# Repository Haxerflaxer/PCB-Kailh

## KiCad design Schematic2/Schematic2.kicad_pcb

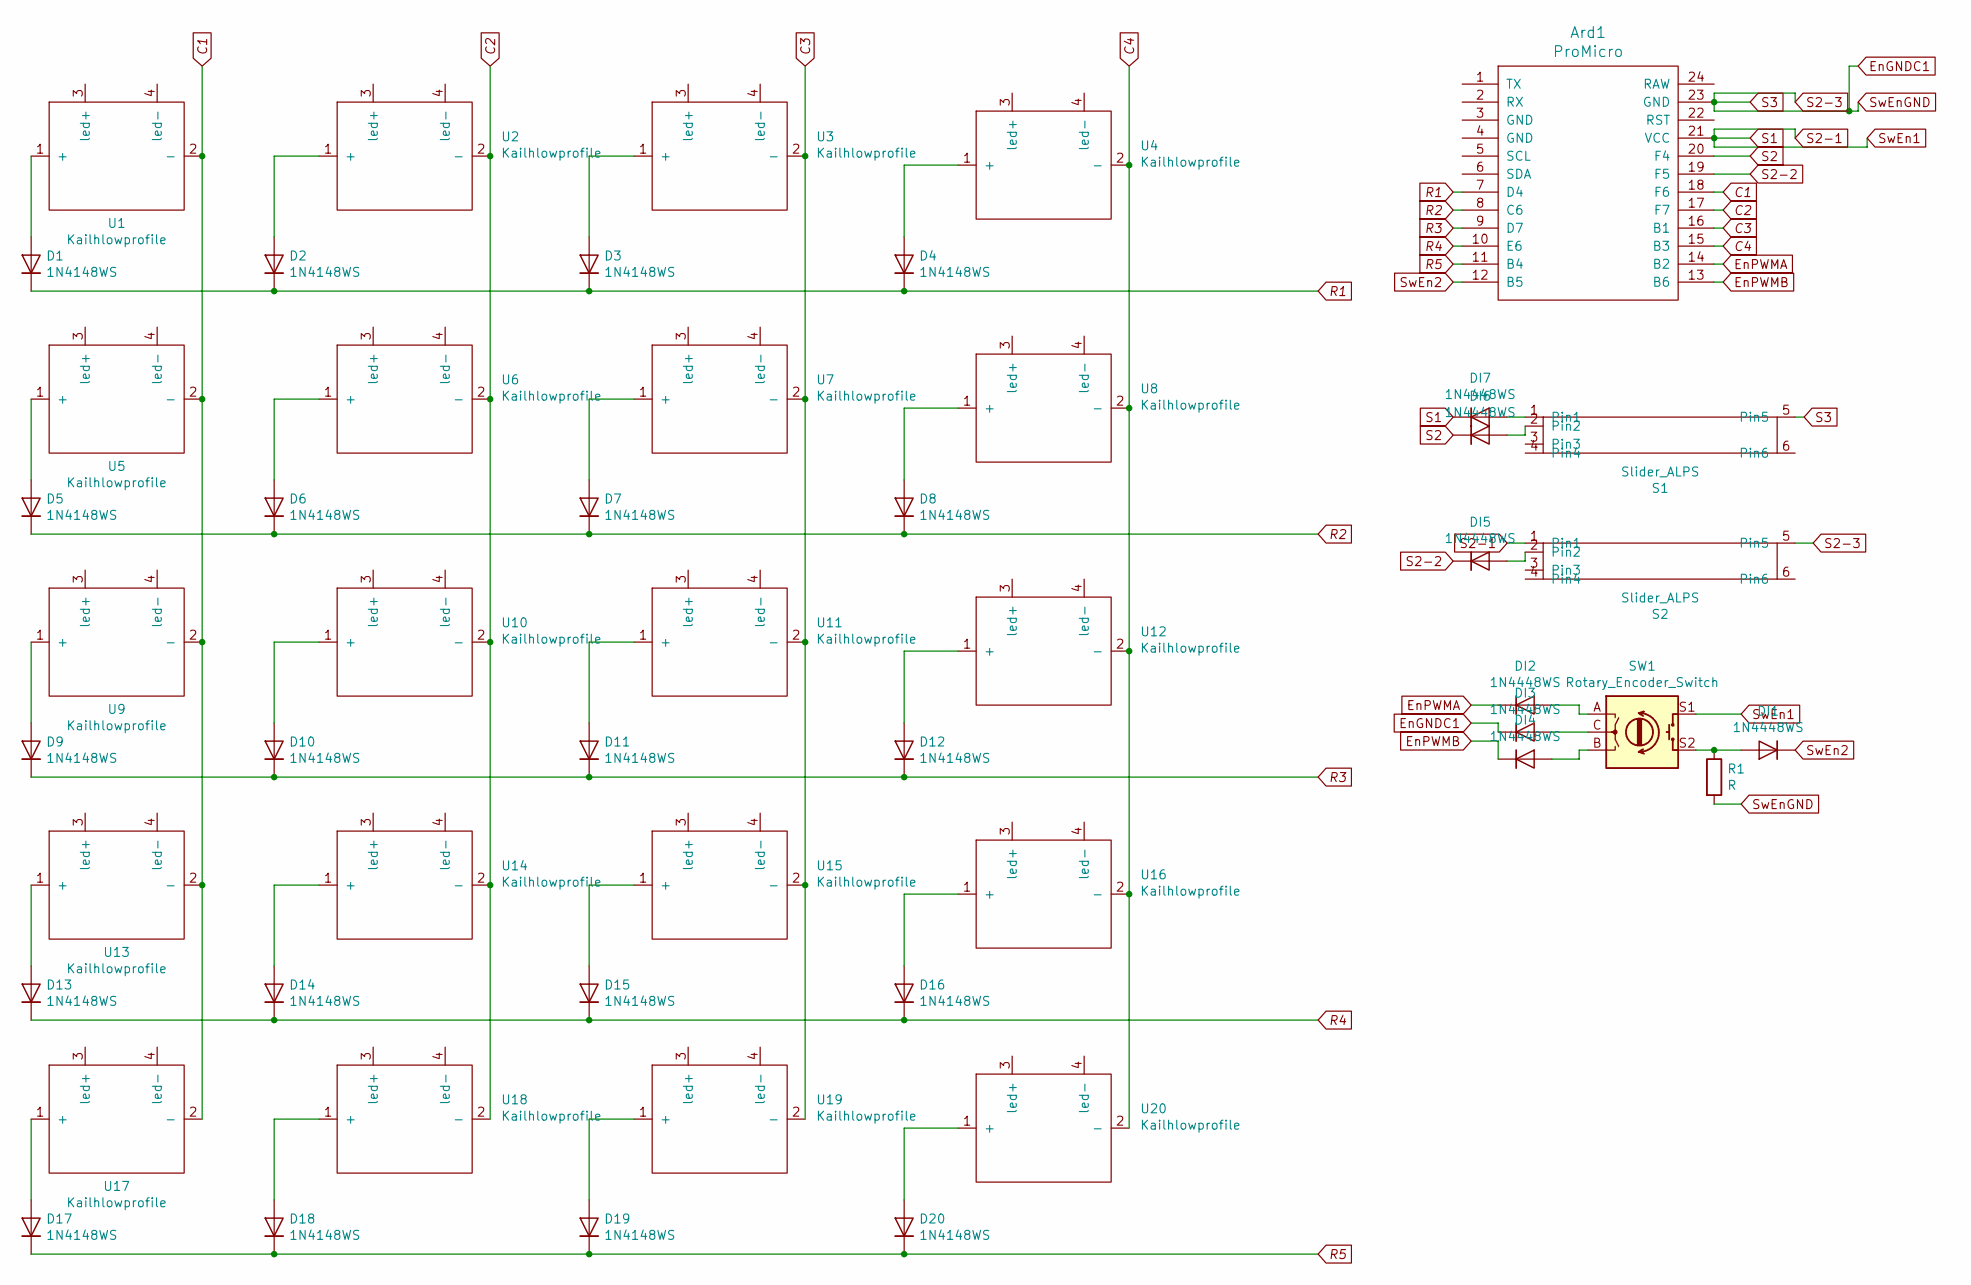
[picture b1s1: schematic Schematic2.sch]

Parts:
Ard1: ProMicro; Pro_Micro
D1, D2, D3, D4, D5, D6, D7, D8, D9, D10, D11, D12, D13, D14, D15, D16, D17, D18, D19, D20: 1N4148WS; D_SOD-323
DI1, DI2, DI3, DI4, DI5, DI6, DI7: 1N4448WS; D_1206_3216Metric_Pad1.42x1.75mm_HandSolder
R1: R; R_Axial_DIN0204_L3.6mm_D1.6mm_P2.54mm_Vertical
S1, S2: Slider_ALPS; ALPS-Slider
SW1: Rotary_Encoder_Switch; RotaryEncoder_Alps_EC11E-Switch_Vertical_H20mm
U1, U2, U3, U4, U5, U6, U7, U8, U9, U10, U11, U12, U13, U14, U15, U16, U17, U18, U19, U20: Kailhlowprofile; Kailh-PG1350-1u-No-Clickhole-No-LED

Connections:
C1: Ard1.18 (F6), U1.2 (-), U5.2 (-), U9.2 (-), U13.2 (-), U17.2 (-)
C2: Ard1.17 (F7), U2.2 (-), U6.2 (-), U10.2 (-), U14.2 (-), U18.2 (-)
C3: Ard1.16 (B1), U3.2 (-), U7.2 (-), U11.2 (-), U15.2 (-), U19.2 (-)
C4: Ard1.15 (B3), U4.2 (-), U8.2 (-), U12.2 (-), U16.2 (-), U20.2 (-)
EnPWMA: Ard1.14 (B2), DI2.1 (K)
EnPWMB: Ard1.13 (B6), DI4.1 (K)
unnamed: D1.2 (A), U1.1 (+)
unnamed: D2.2 (A), U2.1 (+)
unnamed: D3.2 (A), U3.1 (+)
unnamed: D4.2 (A), U4.1 (+)
unnamed: D5.2 (A), U5.1 (+)
unnamed: D6.2 (A), U6.1 (+)
unnamed: D7.2 (A), U7.1 (+)
unnamed: D8.2 (A), U8.1 (+)
unnamed: D9.2 (A), U9.1 (+)
unnamed: D10.2 (A), U10.1 (+)
unnamed: D11.2 (A), U11.1 (+)
unnamed: D12.2 (A), U12.1 (+)
unnamed: D13.2 (A), U13.1 (+)
unnamed: D14.2 (A), U14.1 (+)
unnamed: D15.2 (A), U15.1 (+)
unnamed: D16.2 (A), U16.1 (+)
unnamed: D17.2 (A), U17.1 (+)
unnamed: D18.2 (A), U18.1 (+)
unnamed: D19.2 (A), U19.1 (+)
unnamed: D20.2 (A), U20.1 (+)
unnamed: DI1.2 (A), R1.1, SW1.S2
unnamed: DI2.2 (A), SW1.A
unnamed: DI4.2 (A), SW1.B
unnamed: DI5.2 (A), S2.2 (Pin2)
unnamed: DI6.2 (A), S1.2 (Pin2)
R1: Ard1.7 (D4), D1.1 (K), D2.1 (K), D3.1 (K), D4.1 (K)
R2: Ard1.8 (C6), D5.1 (K), D6.1 (K), D7.1 (K), D8.1 (K)
R3: Ard1.9 (D7), D9.1 (K), D10.1 (K), D11.1 (K), D12.1 (K)
R4: Ard1.10 (E6), D13.1 (K), D14.1 (K), D15.1 (K), D16.1 (K)
R5: Ard1.11 (B4), D17.1 (K), D18.1 (K), D19.1 (K), D20.1 (K)
S2: Ard1.20 (F4), DI6.1 (K)
S2-2: Ard1.19 (F5), DI5.1 (K)
SwEn2: Ard1.12 (B5), DI1.1 (K)

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
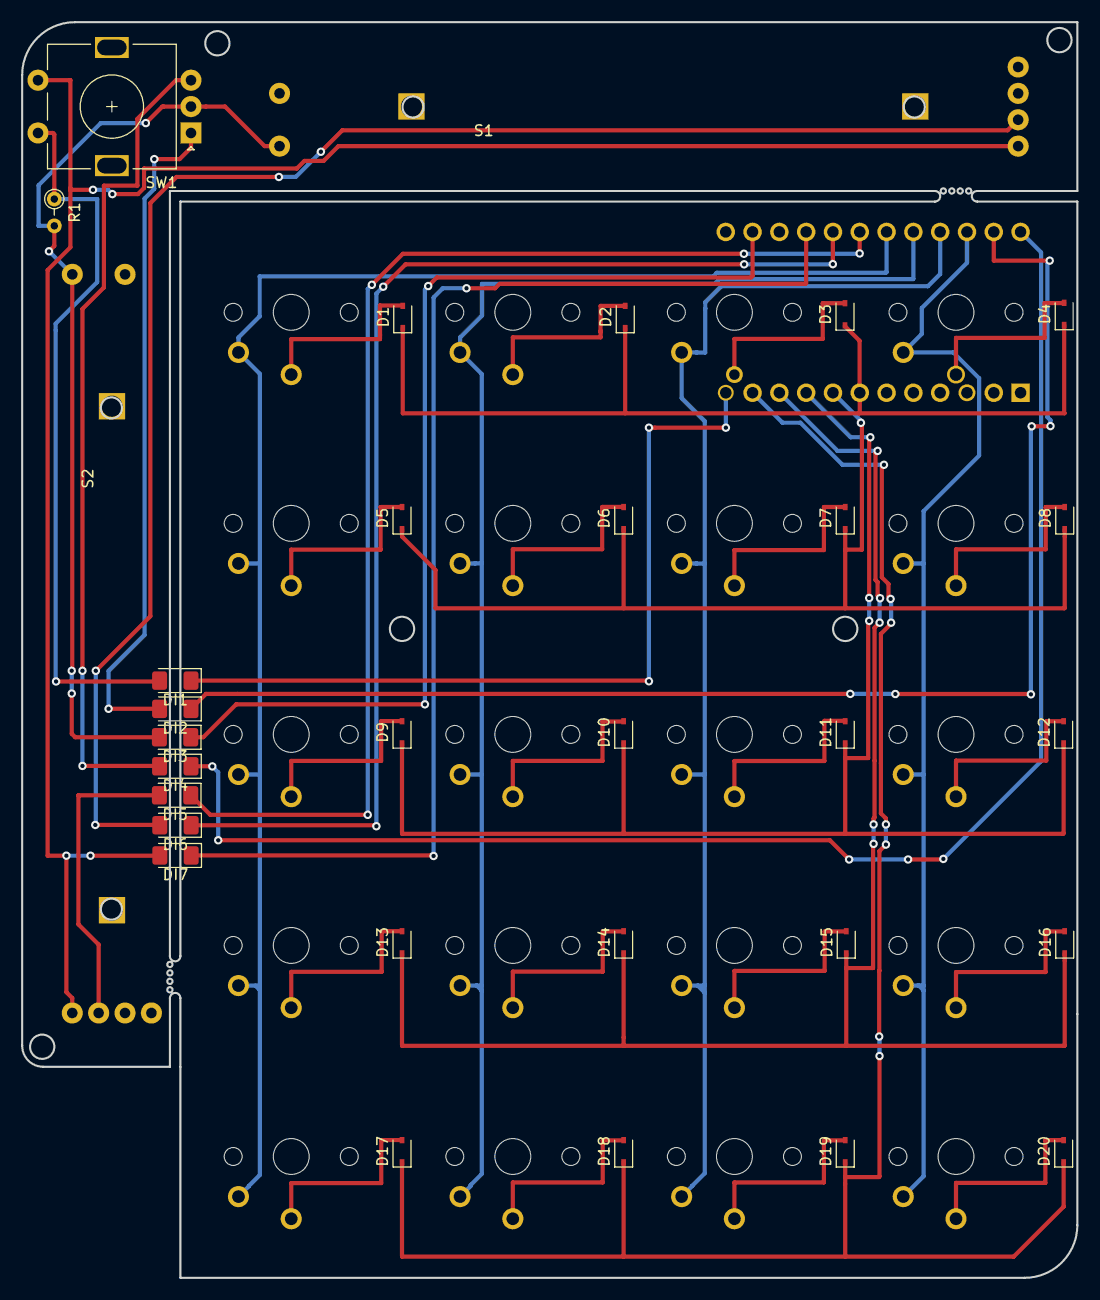
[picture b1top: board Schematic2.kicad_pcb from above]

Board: 2 copper layers, 100.0 x 119.0 mm, 52 parts (1 on the bottom side), 41 nets.

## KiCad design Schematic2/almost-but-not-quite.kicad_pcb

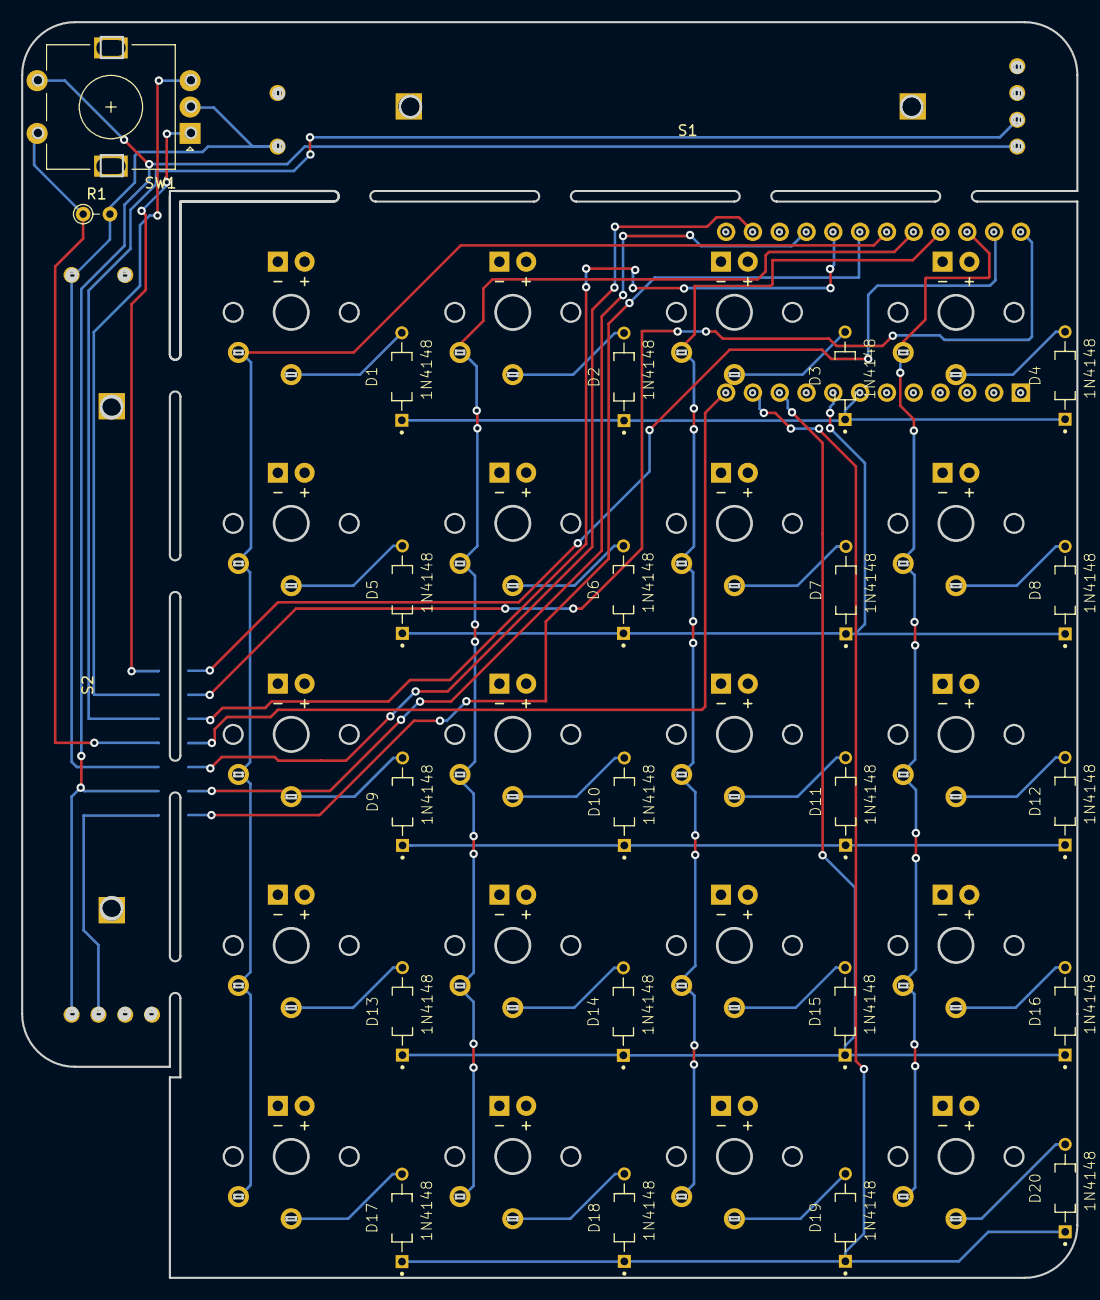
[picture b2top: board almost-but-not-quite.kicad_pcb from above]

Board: 2 copper layers, 100.0 x 119.0 mm, 45 parts (1 on the bottom side), 37 nets.

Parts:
Ard1: ProMicro; Pro_Micro
D1, D2, D3, D4, D5, D6, D7, D8, D9, D10, D11, D12, D13, D14, D15, D16, D17, D18, D19, D20: 1N4148; DIOAD829W49L456D191
R1: R; R_Axial_DIN0204_L3.6mm_D1.6mm_P2.54mm_Vertical
S1, S2: Slider_ALPS; ALPS-Slider
SW1: Rotary_Encoder_Switch; RotaryEncoder_Alps_EC11E-Switch_Vertical_H20mm
U1, U2, U3, U4, U5, U6, U7, U8, U9, U10, U11, U12, U13, U14, U15, U16, U17, U18, U19, U20: Kailhlowprofile; Kailh-PG1350-1u-No-Clickhole

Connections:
C1: Ard1.18, U1.2, U5.2, U9.2, U13.2, U17.2
C2: Ard1.17, U2.2, U6.2, U10.2, U14.2, U18.2
C3: Ard1.16, U3.2, U7.2, U11.2, U15.2, U19.2
C4: Ard1.15, U4.2, U8.2, U12.2, U16.2, U20.2
EnGNDC1: Ard1.3, SW1.C
EnPWMA: Ard1.14, SW1.A
EnPWMB: Ard1.13, SW1.B
unnamed: D1.A, U1.1
unnamed: D2.A, U2.1
unnamed: D3.A, U3.1
unnamed: D4.A, U4.1
unnamed: D5.A, U5.1
unnamed: D6.A, U6.1
unnamed: D7.A, U7.1
unnamed: D8.A, U8.1
unnamed: D9.A, U9.1
unnamed: D10.A, U10.1
unnamed: D11.A, U11.1
unnamed: D12.A, U12.1
unnamed: D13.A, U13.1
unnamed: D14.A, U14.1
unnamed: D15.A, U15.1
unnamed: D16.A, U16.1
unnamed: D17.A, U17.1
unnamed: D18.A, U18.1
unnamed: D19.A, U19.1
unnamed: D20.A, U20.1
R1: Ard1.7, D1.C, D2.C, D3.C, D4.C
R2: Ard1.8, D5.C, D6.C, D7.C, D8.C
R3: Ard1.9, D9.C, D10.C, D11.C, D12.C
R4: Ard1.10, D13.C, D14.C, D15.C, D16.C
R5: Ard1.11, D17.C, D18.C, D19.C, D20.C
S1: Ard1.21, S1.1, S2.1, SW1.S1
S2: Ard1.20, S1.2
S2-2: Ard1.19, S2.2
S2-3: Ard1.23, R1.2, S1.5, S2.5
SwEn2: Ard1.12, R1.1, SW1.S2

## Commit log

2019-03-18 Initialize project
2019-03-18 Footprint lib
2019-03-18 Schematic update
2019-03-18 Updated-latest-keyboard
2019-03-19 Schematic2-real
2019-03-19 Schematic3
    19/03/2019 23:59
2019-03-20 Finalized keyboard schem
    Circuit finished
2019-03-20 THE FINAL
    urgh. Last and final PCB
2019-03-21 New push 2019-03-21
2019-03-21 Update fp-info-cache
2019-03-21 The final countdown
    The diamond deluxe of FINAL
2019-03-22 finished board design
    all done
2019-03-23 Print time - final and absolutely done edition
    This edition is completely done, for realz, and has all the files you need to print a macro keyboard with Kailh switches.
